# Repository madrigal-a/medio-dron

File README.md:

# Medio dron

Proyecto de un medio dron con control: dos motores en un brazo que debe mantenerse en hover y
poder rotar de forma controlada.

## Versiones

| Carpeta | Estado | Qué es |
|---|---|---|
| [`v0-prueba-motores/`](v0-prueba-motores) | ✅ Pruebas | Test de motores EX1103: banco de empuje impreso en 3D y control manual de 2 motores desde una página web. Sirve como base y referencia. |
| [`hardware/`](hardware) | 🚧 En diseño | PCBs en KiCad 9: placa principal (ESP32-C3) y placa de sensores (IMU + barómetro). |
| _próximamente_ | 🚧 | Proyecto completo del medio dron con control. |

## Hardware actual
- Motores Happymodel **EX1103 11000KV** (1S–2S) con ESC BLHeli_S / Bluejay por **DShot300**
- **ESP32** DevKit · señal en D13 (motor 1) y D15 (motor 2)
- Fuente de laboratorio a **7.4 V** (nunca 12 V)

Detalles de conexión y uso en el README de cada carpeta.

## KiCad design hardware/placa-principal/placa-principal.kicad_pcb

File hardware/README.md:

# Medio dron — hardware (KiCad 9)

Dos PCBs de 2 capas que comparten una librería propia. Abrir con **KiCad 9 o más nuevo**.

```
lib/                 símbolos, huellas y modelos 3D propios (medio_dron)
placa-principal/     ESP32-C3-MINI-1U, USB-C, LDO, ESC, Qwiic, ToF      33 × 26.4 mm
placa-sensores/      LSM6DSV16X + ICP-20100, Qwiic                      22 × 13 mm
```

En cada carpeta:
- `*.kicad_pro / .kicad_sch / .kicad_pcb` — proyecto, esquemático y placa.
- `*.pdf` — esquemático. `bom.csv` — lista de materiales.
- `img/` — renders 3D y plano de ensamble (referencias de cada componente).
- `fab/` — Gerbers + taladros (zip listo para JLCPCB) y archivo de posiciones.

| Placa principal | Placa de sensores |
|---|---|
|  |  |

## Estado
- [x] Esquemáticos v1.0 (ERC sin errores)
- [x] Layout v1.0 (DRC: 0 violaciones, 0 sin conectar, coincide con el esquemático)
- [ ] Revisión a mano antes de mandar a fabricar
- [ ] Pedido de PCBs + esténcil

## Reglas de diseño
Pista mínima 0.2 mm, separación 0.15 mm, vías 0.6/0.3 mm, 2 capas, plano de GND en ambas caras.
Pedir **esténcil** (capa F.Paste). Grosor recomendado: 1.0 mm (0.8 mm para la de sensores).

## Placa principal — pines del ESP32-C3
| GPIO | Uso |
|---|---|
| 0, 1 | SDA, SCL (Qwiic, pull-ups 2.2 k) |
| 2 | pull-up 10 k (pin de arranque) |
| 3 | VBAT por divisor 100 k / 27 k (ADC1_CH3) |
| 4 | ToF Pololu OUT |
| 5 | libre |
| 6, 7 | DShot ESC1, ESC2 |
| 8 | pull-up 10 k (pin de arranque) |
| 9 | botón BOOT |
| 10 | libre |
| 18, 19 | USB D−, D+ |
| 20 | LED (activo en alto) |
| 21 | libre (TX de arranque) |

Alimentación: batería 2S o USB → diodos Schottky → TLV76733 → 3.3 V.
Conectores de batería, ToF y ESC: huecos de 2.54 mm para soldar cables (rotulados por la cara de abajo).
El módulo es **MINI-1U**: necesita antena externa de 2.4 GHz con conector U.FL.

## Placa de sensores
- LSM6DSV16X en I²C **0x6A** (SA0 a GND). INT1 sale a un pad de prueba.
- ICP-20100 en I²C **0x63**. Su INT queda sin conectar.
- Sin pull-ups (están en la placa principal). Va en el brazo que se inclina.
- La huella del ICP-20100 se hizo con el patrón de la nota AN-000140 de TDK y el pin-out del datasheet DS-000416.

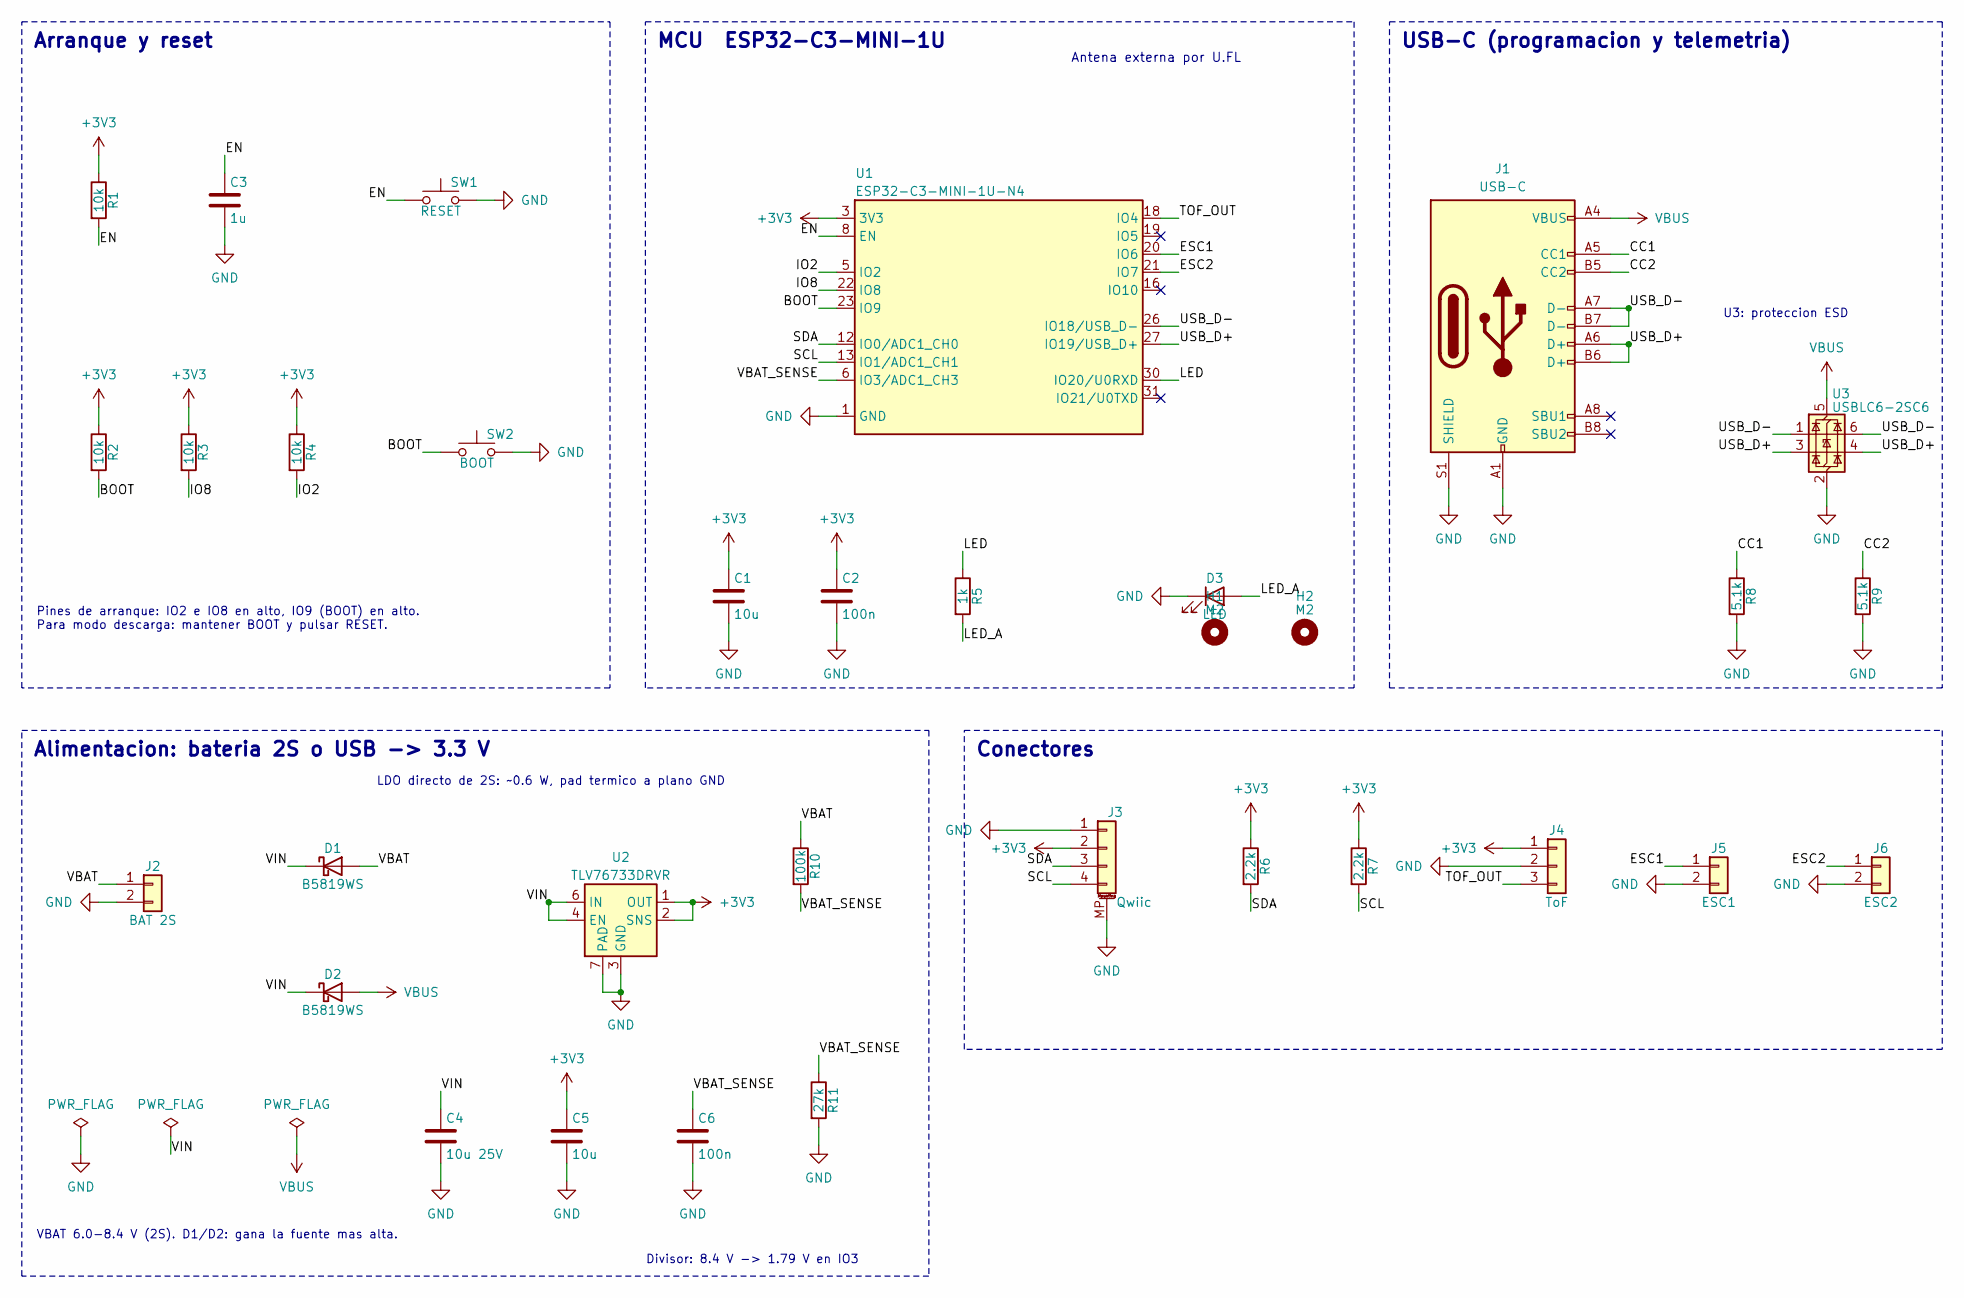
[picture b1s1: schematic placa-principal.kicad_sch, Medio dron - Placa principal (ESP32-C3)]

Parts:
C1, C5: 10u; C_0603_1608Metric
C2, C6: 100n; C_0603_1608Metric
C3: 1u; C_0603_1608Metric
C4: 10u 25V; C_0805_2012Metric
D1, D2: B5819WS; D_SOD-323; MPN B5819WS
D3: LED; LED_0603_1608Metric
H1, H2: M2; MountingHole_2.2mm_M2
J1: USB-C; USB_C_Receptacle_GCT_USB4105-xx-A_16P_TopMnt_Horizontal; MPN USB4105-GF-A
J2: BAT 2S; PinHeader_1x02_P2.54mm_Vertical
J3: Qwiic; JST_SH_SM04B-SRSS-TB_1x04-1MP_P1.00mm_Horizontal; MPN SM04B-SRSS-TB
J4: ToF; PinHeader_1x03_P2.54mm_Vertical
J5: ESC1; PinHeader_1x02_P2.54mm_Vertical
J6: ESC2; PinHeader_1x02_P2.54mm_Vertical
R1, R2, R3, R4: 10k; R_0603_1608Metric
R5: 1k; R_0603_1608Metric
R6, R7: 2.2k; R_0603_1608Metric
R8, R9: 5.1k; R_0603_1608Metric
R10: 100k; R_0603_1608Metric
R11: 27k; R_0603_1608Metric
SW1: RESET; SW_Push_1P1T_NO_CK_KMR2; MPN KMR221GLFS
SW2: BOOT; SW_Push_1P1T_NO_CK_KMR2; MPN KMR221GLFS
U1: ESP32-C3-MINI-1U-N4; ESP32-C3-MINI-1U; MPN ESP32-C3-MINI-1U-N4X
U2: TLV76733DRVR; WSON-6-1EP_2x2mm_P0.65mm_EP1x1.6mm; MPN TLV76733DRVR
U3: USBLC6-2SC6; SOT-23-6; MPN USBLC6-2SC6

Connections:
+3V3: C1.1, C2.1, C5.1, J3.2, J4.1, R1.1, R2.1, R3.1, R4.1, R6.1, R7.1, U1.3 (3V3), U2.1 (OUT), U2.2 (SNS)
/BOOT: R2.2, SW2.1, U1.23 (IO9)
/CC1: J1.A5 (CC1), R8.1
/CC2: J1.B5 (CC2), R9.1
/EN: C3.1, R1.2, SW1.1, U1.8 (EN)
/ESC1: J5.1, U1.20 (IO6)
/ESC2: J6.1, U1.21 (IO7)
/IO2: R4.2, U1.5 (IO2)
/IO8: R3.2, U1.22 (IO8)
/LED: R5.1, U1.30 (IO20/U0RXD)
/LED_A: D3.2 (A), R5.2
/SCL: J3.4, R7.2, U1.13 (IO1/ADC1_CH1)
/SDA: J3.3, R6.2, U1.12 (IO0/ADC1_CH0)
/TOF_OUT: J4.3, U1.18 (IO4)
/USB_D+: J1.A6 (D+), J1.B6 (D+), U1.27 (IO19/USB_D+), U3.3 (I/O2), U3.4 (I/O2)
/USB_D-: J1.A7 (D-), J1.B7 (D-), U1.26 (IO18/USB_D-), U3.1 (I/O1), U3.6 (I/O1)
/VBAT: D1.2 (A), J2.1, R10.1
/VBAT_SENSE: C6.1, R10.2, R11.1, U1.6 (IO3/ADC1_CH3)
/VIN: C4.1, D1.1 (K), D2.1 (K), U2.4 (EN), U2.6 (IN)
GND: C1.2, C2.2, C3.2, C4.2, C5.2, C6.2, D3.1 (K), J1.A1 (GND), J1.A12 (GND), J1.B1 (GND), J1.B12 (GND), J1.S1 (SHIELD), J2.2, J3.1, J3.MP (MountPin), J4.2, J5.2, J6.2, R8.2, R9.2, R11.2, SW1.2, SW2.2, U1.1 (GND), U1.2 (GND), U1.11 (GND), U1.14 (GND), U1.36 (GND), U1.37 (GND), U1.38 (GND), U1.39 (GND), U1.40 (GND), U1.41 (GND), U1.42 (GND), U1.43 (GND), U1.44 (GND), U1.45 (GND), U1.46 (GND), U1.47 (GND), U1.48 (GND), U1.49 (GND), U1.50 (GND), U1.51 (GND), U1.52 (GND), U1.53 (GND), U2.3 (GND), U2.5 (GND), U2.7 (PAD), U3.2 (GND)
VBUS: D2.2 (A), J1.A4 (VBUS), J1.A9 (VBUS), J1.B4 (VBUS), J1.B9 (VBUS), U3.5 (VBUS)

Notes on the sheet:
MCU ESP32-C3-MINI-1U
Antena externa por U.FL
Arranque y reset
Pines de arranque: IO2 e IO8 en alto, IO9 (BOOT) en alto. Para modo descarga: mantener BOOT y pulsar RESET.
USB-C (programacion y telemetria)
U3: proteccion ESD
Alimentacion: bateria 2S o USB -> 3.3 V
VBAT 6.0-8.4 V (2S). D1/D2: gana la fuente mas alta.
Divisor: 8.4 V -> 1.79 V en IO3
LDO directo de 2S: ~0.6 W, pad termico a plano GND
Conectores

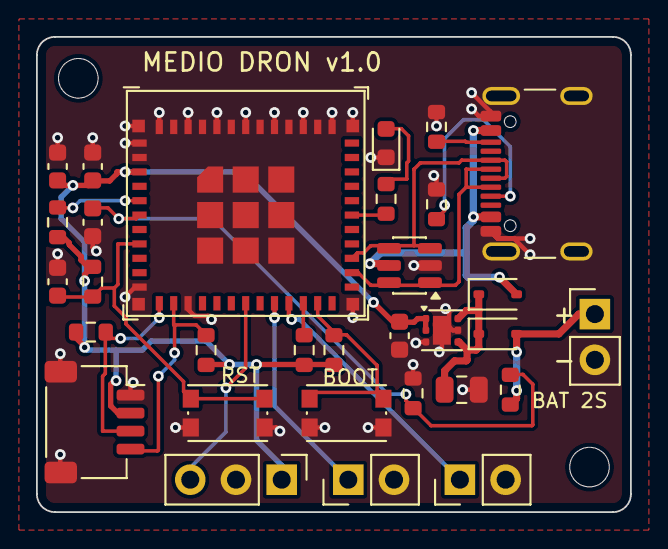
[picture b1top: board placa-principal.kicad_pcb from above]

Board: 2 copper layers, 33.0 x 26.4 mm, 33 parts (0 on the bottom side), 21 nets.

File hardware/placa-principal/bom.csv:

"Reference","Value","Footprint","MPN","QUANTITY"
"C1,C5","10u","Capacitor_SMD:C_0603_1608Metric","","2"
"C2,C6","100n","Capacitor_SMD:C_0603_1608Metric","","2"
"C3","1u","Capacitor_SMD:C_0603_1608Metric","","1"
"C4","10u 25V","Capacitor_SMD:C_0805_2012Metric","","1"
"D1,D2","B5819WS","Diode_SMD:D_SOD-323","B5819WS","2"
"D3","LED","LED_SMD:LED_0603_1608Metric","","1"
"J1","USB-C","Connector_USB:USB_C_Receptacle_GCT_USB4105-xx-A_16P_TopMnt_Horizontal","USB4105-GF-A","1"
"J2","BAT 2S","Connector_PinHeader_2.54mm:PinHeader_1x02_P2.54mm_Vertical","","1"
"J3","Qwiic","Connector_JST:JST_SH_SM04B-SRSS-TB_1x04-1MP_P1.00mm_Horizontal","SM04B-SRSS-TB","1"
"J4","ToF","Connector_PinHeader_2.54mm:PinHeader_1x03_P2.54mm_Vertical","","1"
"J5","ESC1","Connector_PinHeader_2.54mm:PinHeader_1x02_P2.54mm_Vertical","","1"
"J6","ESC2","Connector_PinHeader_2.54mm:PinHeader_1x02_P2.54mm_Vertical","","1"
"R1-R4","10k","Resistor_SMD:R_0603_1608Metric","","4"
"R5","1k","Resistor_SMD:R_0603_1608Metric","","1"
"R6,R7","2.2k","Resistor_SMD:R_0603_1608Metric","","2"
"R8,R9","5.1k","Resistor_SMD:R_0603_1608Metric","","2"
"R10","100k","Resistor_SMD:R_0603_1608Metric","","1"
"R11","27k","Resistor_SMD:R_0603_1608Metric","","1"
"SW1","RESET","Button_Switch_SMD:SW_Push_1P1T_NO_CK_KMR2","KMR221GLFS","1"
"SW2","BOOT","Button_Switch_SMD:SW_Push_1P1T_NO_CK_KMR2","KMR221GLFS","1"
"U1","ESP32-C3-MINI-1U-N4","medio_dron:ESP32-C3-MINI-1U","ESP32-C3-MINI-1U-N4X","1"
"U2","TLV76733DRVR","Package_SON:WSON-6-1EP_2x2mm_P0.65mm_EP1x1.6mm","TLV76733DRVR","1"
"U3","USBLC6-2SC6","Package_TO_SOT_SMD:SOT-23-6","USBLC6-2SC6","1"

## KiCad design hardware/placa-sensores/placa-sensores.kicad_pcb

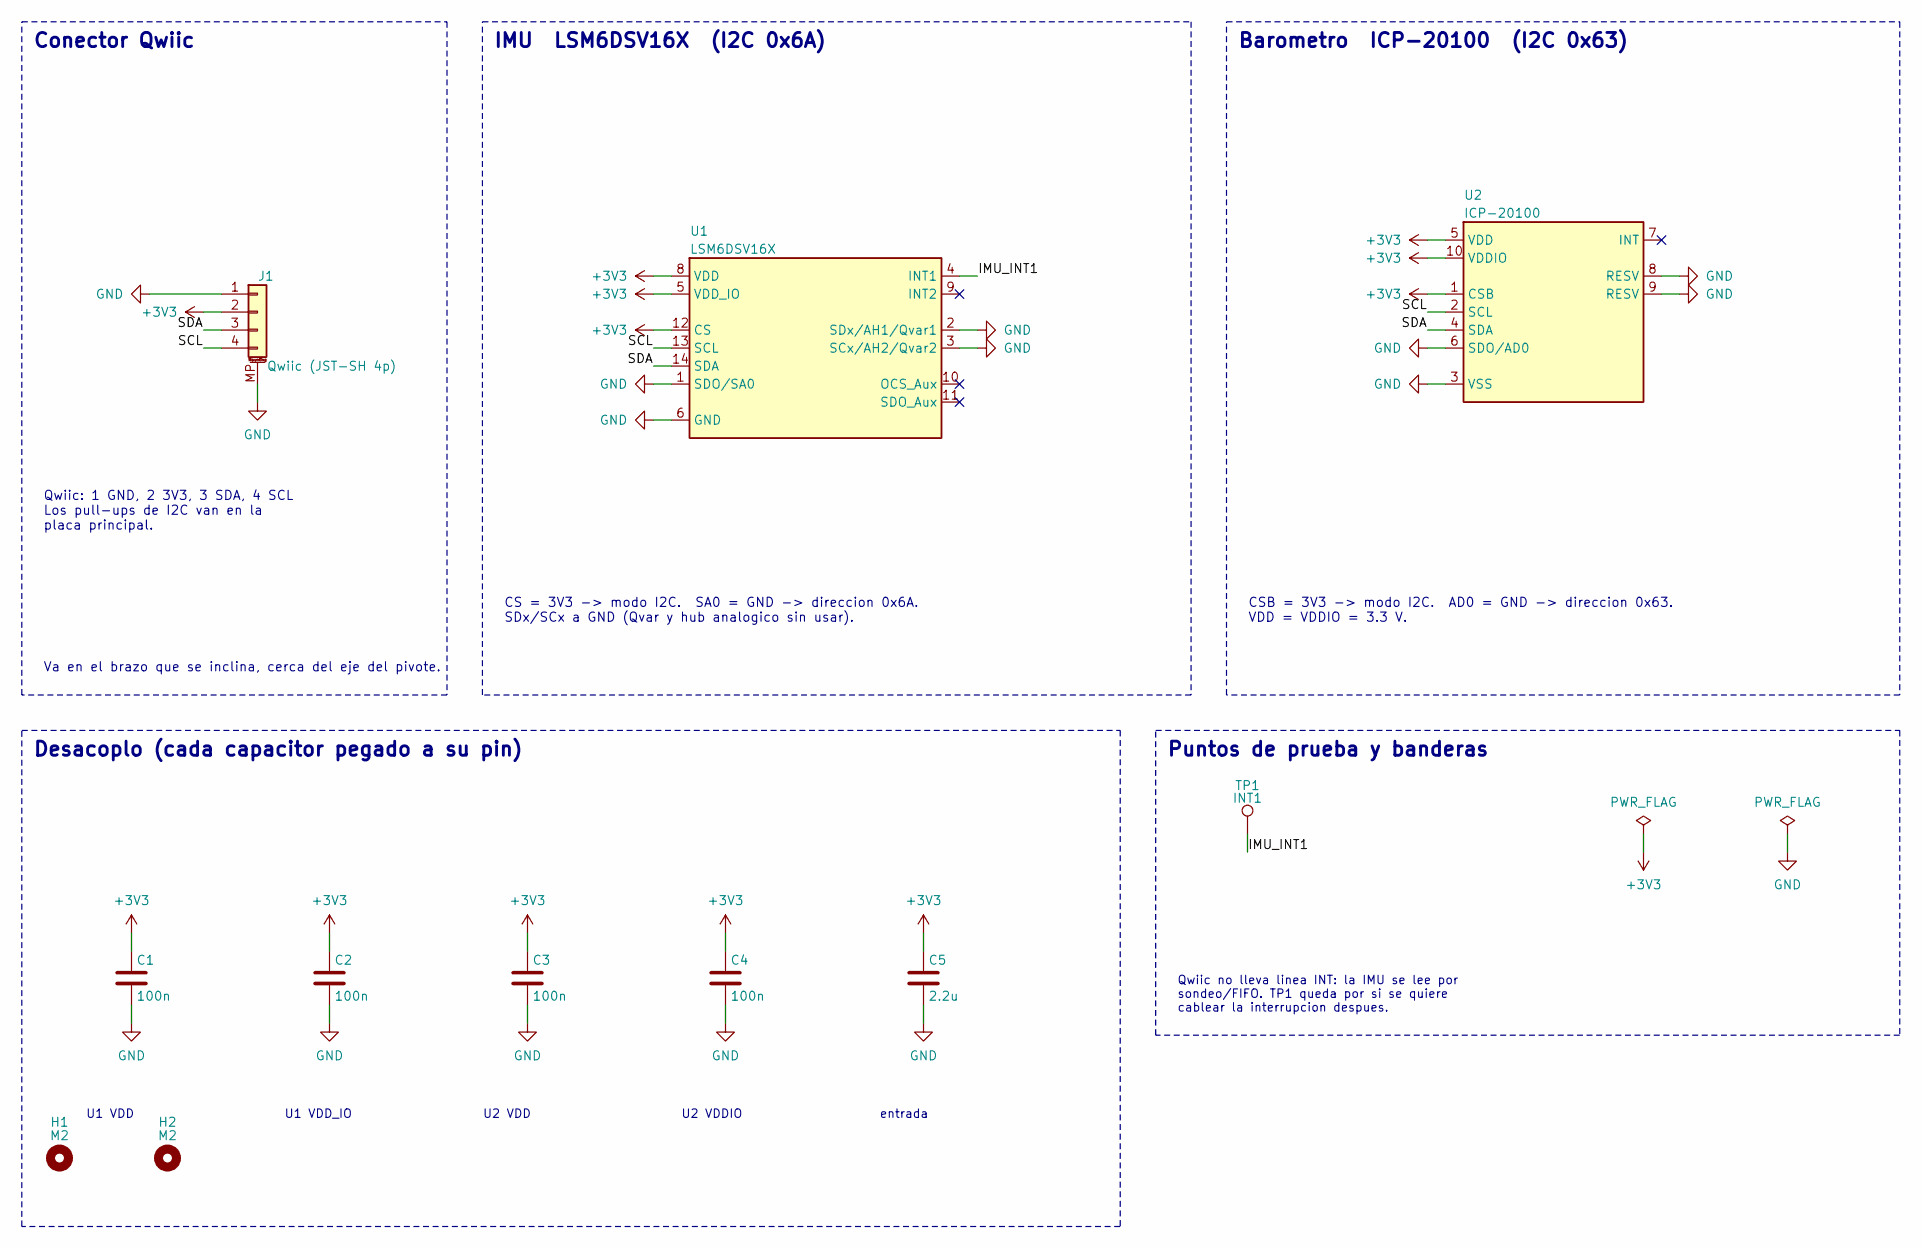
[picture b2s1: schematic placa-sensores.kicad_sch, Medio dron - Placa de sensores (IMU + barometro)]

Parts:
C1, C2, C3, C4: 100n; C_0603_1608Metric
C5: 2.2u; C_0603_1608Metric
H1, H2: M2; MountingHole_2.2mm_M2
J1: Qwiic (JST-SH 4p); JST_SH_SM04B-SRSS-TB_1x04-1MP_P1.00mm_Horizontal; MPN SM04B-SRSS-TB
TP1: INT1; TestPoint_Pad_D1.0mm
U1: LSM6DSV16X; LGA-14_3x2.5mm_P0.5mm_LayoutBorder3x4y; MPN LSM6DSV16XTR
U2: ICP-20100; TDK_ICP-20100_LGA-10_2x2mm_P0.5mm; MPN ICP-20100

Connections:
+3V3: C1.1, C2.1, C3.1, C4.1, C5.1, J1.2, U1.5 (VDD_IO), U1.8 (VDD), U1.12 (CS), U2.1 (CSB), U2.5 (VDD), U2.10 (VDDIO)
/IMU_INT1: TP1.1, U1.4 (INT1)
/SCL: J1.4, U1.13 (SCL), U2.2 (SCL)
/SDA: J1.3, U1.14 (SDA), U2.4 (SDA)
GND: C1.2, C2.2, C3.2, C4.2, C5.2, J1.1, J1.MP (MountPin), U1.1 (SDO/SA0), U1.2 (SDx/AH1/Qvar1), U1.3 (SCx/AH2/Qvar2), U1.6 (GND), U1.7 (GND), U2.3 (VSS), U2.6 (SDO/AD0), U2.8 (RESV), U2.9 (RESV)

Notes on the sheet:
Conector Qwiic
Qwiic: 1 GND, 2 3V3, 3 SDA, 4 SCL Los pull-ups de I2C van en la placa principal.
IMU LSM6DSV16X (I2C 0x6A)
CS = 3V3 -> modo I2C. SA0 = GND -> direccion 0x6A. SDx/SCx a GND (Qvar y hub analogico sin usar).
Barometro ICP-20100 (I2C 0x63)
CSB = 3V3 -> modo I2C. AD0 = GND -> direccion 0x63. VDD = VDDIO = 3.3 V.
Desacoplo (cada capacitor pegado a su pin)
U1 VDD
U1 VDD_IO
U2 VDD
U2 VDDIO
entrada
Puntos de prueba y banderas
Va en el brazo que se inclina, cerca del eje del pivote.
Qwiic no lleva linea INT: la IMU se lee por sondeo/FIFO. TP1 queda por si se quiere cablear la interrupcion despues.

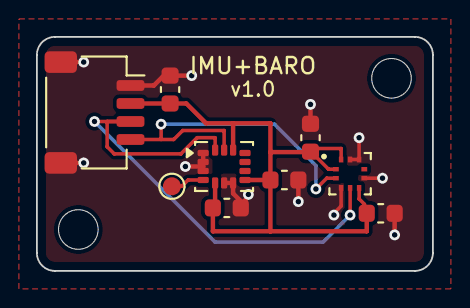
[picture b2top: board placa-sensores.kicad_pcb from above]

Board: 2 copper layers, 22.0 x 13.0 mm, 11 parts (0 on the bottom side), 5 nets.

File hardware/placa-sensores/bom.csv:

"Reference","Value","Footprint","MPN","QUANTITY"
"C1-C4","100n","Capacitor_SMD:C_0603_1608Metric","","4"
"C5","2.2u","Capacitor_SMD:C_0603_1608Metric","","1"
"J1","Qwiic (JST-SH 4p)","Connector_JST:JST_SH_SM04B-SRSS-TB_1x04-1MP_P1.00mm_Horizontal","SM04B-SRSS-TB","1"
"TP1","INT1","TestPoint:TestPoint_Pad_D1.0mm","","1"
"TP2","INT_BARO","TestPoint:TestPoint_Pad_D1.0mm","","1"
"U1","LSM6DSV16X","Package_LGA:LGA-14_3x2.5mm_P0.5mm_LayoutBorder3x4y","LSM6DSV16XTR","1"
"U2","ICP-20100","medio_dron:TDK_ICP-20100_LGA-10_2x2mm_P0.5mm","ICP-20100","1"
